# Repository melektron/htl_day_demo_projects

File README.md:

# HTL-Day projects
Consists of a few projects created for the HTL-Anichstraße as part of the HTL-Day convention.

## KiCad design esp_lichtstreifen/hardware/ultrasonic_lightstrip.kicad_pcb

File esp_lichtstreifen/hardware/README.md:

# ultrasonic light strip board

This board connects an HC-SR04 ultrasonic sensor, OLED display and WS2812B LED-Strip to an ESP32 DevKitC.
It also includes a barrel jack for power.

## Dependencies

This project requires the Espressif KiCAD libs.

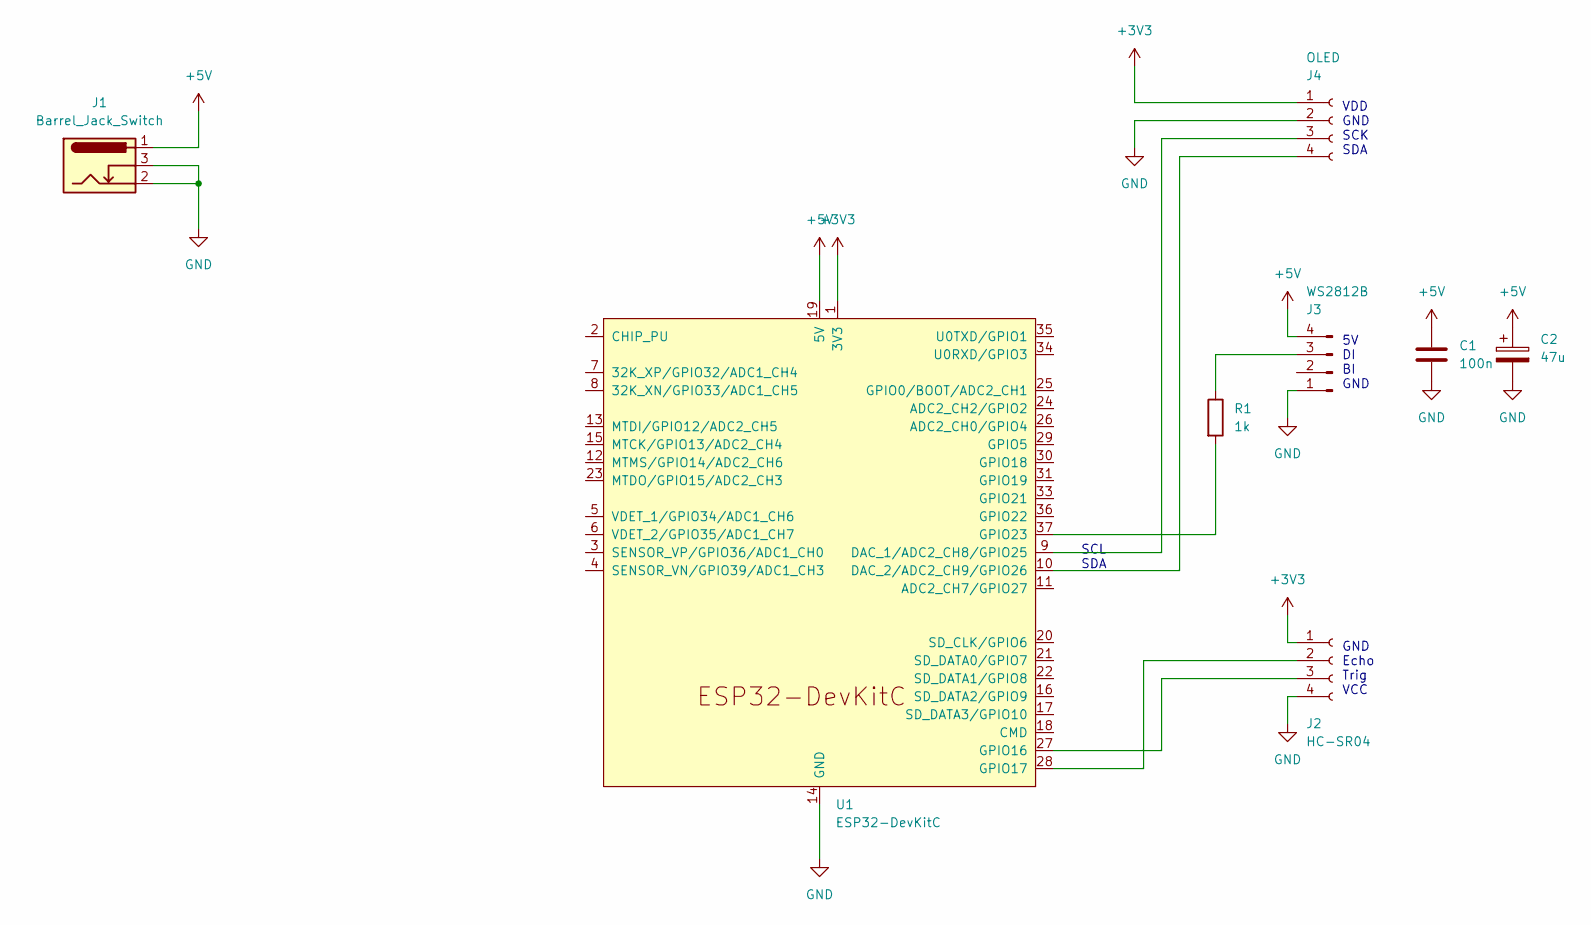
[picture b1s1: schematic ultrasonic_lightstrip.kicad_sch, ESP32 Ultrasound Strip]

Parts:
C1: 100n; C_Disc_D6.0mm_W2.5mm_P5.00mm
C2: 47u; CP_Radial_D8.0mm_P3.80mm
J1: Barrel_Jack_Switch; BarrelJack_Horizontal
J2: HC-SR04; PinSocket_1x04_P2.54mm_Horizontal
J3: WS2812B; PinHeader_1x04_P2.54mm_Horizontal
J4: OLED; PinSocket_1x04_P2.54mm_Vertical
R1: 1k; R_Axial_DIN0207_L6.3mm_D2.5mm_P10.16mm_Horizontal
U1: ESP32-DevKitC

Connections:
+3V3: J2.1, J4.1, U1.1 (3V3)
+5V: C1.1, C2.1, J1.1, J3.4, U1.19 (5V)
GND: C1.2, C2.2, J1.2, J1.3, J2.4, J3.1, J4.2, U1.14 (GND), U1.32 (GND), U1.38 (GND)
unnamed: J2.2, U1.28 (GPIO17)
unnamed: J2.3, U1.27 (GPIO16)
unnamed: J3.3, R1.1
unnamed: J4.3, U1.9 (DAC_1/ADC2_CH8/GPIO25)
unnamed: J4.4, U1.10 (DAC_2/ADC2_CH9/GPIO26)
unnamed: R1.2, U1.37 (GPIO23)

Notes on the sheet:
VDD GND SCK SDA
GND Echo Trig VCC
SCL SDA
5V DI BI GND

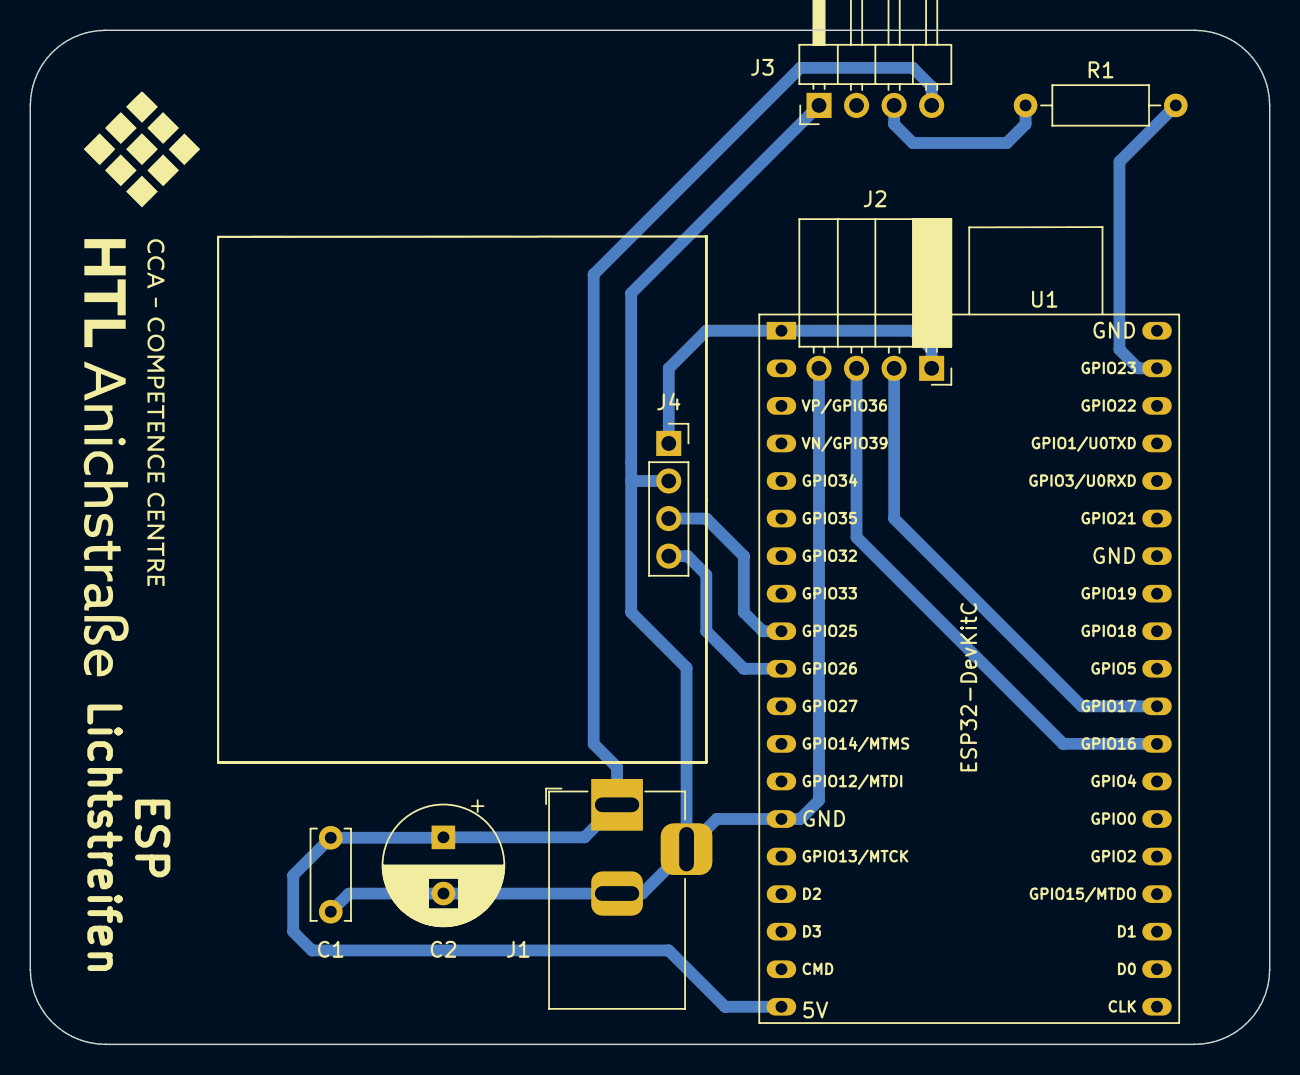
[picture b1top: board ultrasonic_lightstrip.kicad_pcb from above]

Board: 2 copper layers, 83.8 x 68.6 mm, 8 parts (0 on the bottom side), 9 nets.

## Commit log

2022-10-10 PIO setup
2022-10-10 added test code
2022-10-10 added servo experiments and led matrix gfx impl
2022-10-10 got GFX driver working well enough, added some gfx tests
2022-10-11 got sorting to work
2022-10-11 added webinterface and cleaned up codebase
2022-10-12 worked on animations
2022-10-12 added random_object
2022-10-12 added toco16
2022-10-13 addded main_loop()
2022-10-14 adapted brightness
2022-10-14 addded LEDStrip
2022-10-15 tried to improve and update sorter code
2022-10-15 added temporary color calibration value
2022-10-15 added 8*8 panel
2022-10-15 added text
2023-09-20 added lichtstreifen code
2023-09-20 added folder to code workspace
2023-09-20 base structure
2023-09-20 led bar driver done
2023-09-20 added documentation
2023-09-20 added display
2023-09-20 distance_driver
2023-09-20 all done
2023-09-20 worked on pcb
2023-09-27 pin changes
2023-09-27 fixed flickering
2023-09-27 finished first revision of PCB
2023-09-28 configured values (hehe)
2023-10-02 created branch
2023-10-04 animation changes
2023-10-04 added code
2023-10-04 doesn't exceed 100% anymore
2023-10-04 added idling for display
2023-10-04 brightness chagnagnagnanges
2023-10-04 added x_y_axes control
2023-10-10 removed idle oled
2023-10-10 changed variables
2023-10-10 fixed bugs
2023-10-11 classify
2023-10-12 fixed ledmatrix pin
